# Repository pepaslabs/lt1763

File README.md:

# lt1763

A low-noise supply based on the [LT1763](http://cds.linear.com/docs/en/datasheet/1763fh.pdf).

Schematic: [pdf](kicad/releases/v1/supply.pdf)

OSHPark: [link](https://oshpark.com/shared_projects/uVr4yDgz)

Gerbers: [zip](kicad/releases/v1/gerbers.zip)

# Input filter

The board has provisions for an RLC input filter (see schematic components R4, L1, C3).

You can populate these components with whatever values you like.  I used [this RLC calculator](http://sim.okawa-denshi.jp/en/RLCtool.php) to analyze a few component values.

Note: C3 should be a film capacitor, e.g. Kemet R82 ([4.7uF](https://www.digikey.com/product-detail/en/kemet/R82CC4470AA30J/399-6028-ND/2704682), [1uF](https://www.digikey.com/product-detail/en/kemet/R82DC4100AA60J/399-5860-ND/2571295)).

Note: L1 should be a small-signal axial inductor ([470uH](https://www.digikey.com/product-detail/en/bourns-inc/78F471J-RC/M10142-ND/1306000), [100uH](https://www.digikey.com/product-detail/en/bourns-inc/78F101J-RC/M10136-ND/1305994)).  Note that the 470uH inductor will saturate if more than 90mA is passed.  This board is intended for use with e.g. an LTZ1000 circuit, which only draws about 30mA.

Note: A 10R resistor passing 30mA will add 0.3V of dropout.

## 10R, 100uH, 1uF

## 10R, 470uH, 4.7uF

# Mounting holes

The mounting holes are intended for use with M3 brass hex stand-offs.

# Lead spacing

The input and output leads fall on a 0.1" grid (breadboard compatible).

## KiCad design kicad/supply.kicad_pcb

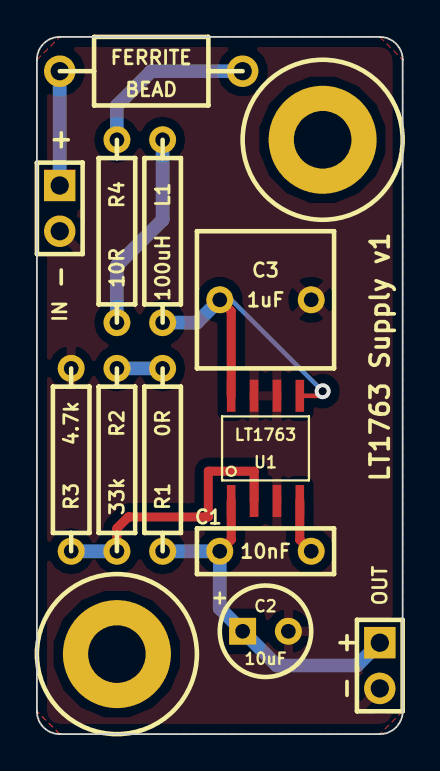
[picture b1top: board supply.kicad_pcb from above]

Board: 2 copper layers, 20.3 x 38.7 mm, 14 parts (0 on the bottom side), 9 nets.

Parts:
C1: 10nF; BOXCAP_01_03_02_059A
C2: 10uF; ELCAP_10_20_V_059A
C3: 1uF; BOXCAP_02_03_03_059A
FERRITE: BEAD; FERRITE_AXIAL_04_069A
H***: Val**; hole_M3
H***#2: Val**; hole_M3
L1: 100uH; R_AXIAL_0W25_059A_PL
P1, P2: CONN_2X1; SIL-2
R1: 0R; R_AXIAL_0W25_059A_PL
R2: 33k; R_AXIAL_0W25_059A_PL
R3: 4.7k; R_AXIAL_0W25_059A_PL
R4: 10R; R_AXIAL_0W25_059A_PL
U1: LT1763; SO-8

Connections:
GND: C2.2, C3.2, P1.2, P2.2, R3.2, U1.3, U1.6, U1.7
unnamed: C1.1, C2.1, P2.1, R1.1, U1.1
unnamed: C1.2, U1.4
unnamed: R2.2, R3.1, U1.2
unnamed: R1.2, R2.1
unnamed: L1.1, R4.2
unnamed: FERRITE.1, P1.1
unnamed: C3.1, L1.2, U1.5, U1.8
unnamed: FERRITE.2, R4.1

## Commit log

2018-02-24 initial release
2018-02-24 board shots, readme
2018-02-24 readme
